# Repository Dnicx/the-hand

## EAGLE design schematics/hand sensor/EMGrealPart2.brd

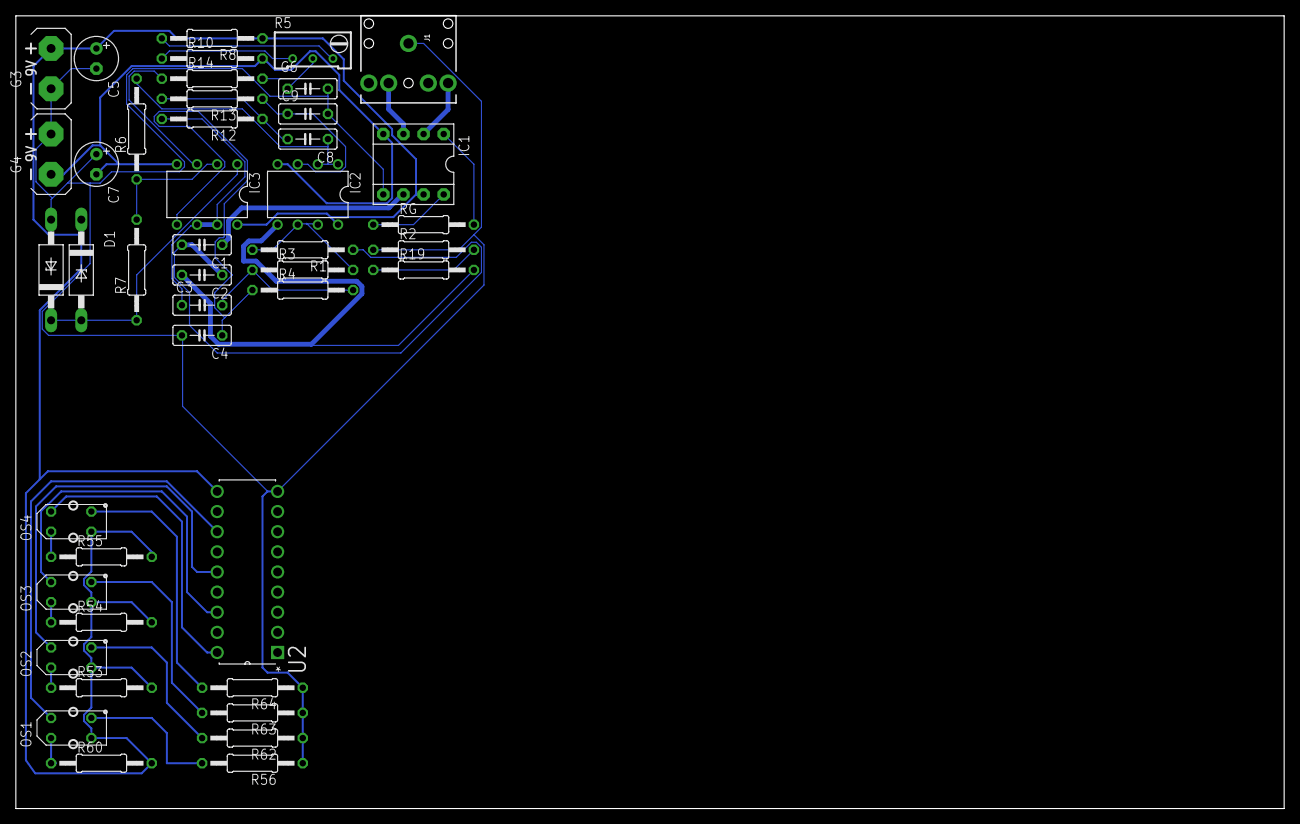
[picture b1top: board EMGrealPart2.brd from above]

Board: 2 copper layers, 160.0 x 100.0 mm, 44 parts (0 on the bottom side), 36 nets.

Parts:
C1, C2: 220nF; C050-025X075
C3: 33nF; C050-025X075
C4: 22nF; C050-025X075
C5, C7: 100u; E2,5-6
C6, C9: 10nF; C050-025X075
C8: 100nF; C050-025X075
D1, D2: F126Z12
G3, G4: DC 9V AC 0; AB9V
IC1: INA118P; DIL08
IC2, IC3: OP275P; DIL08
J1: AUDIO_JACK_3.5MM_PTH; AUDIO-JACK
OS1, OS2, OS3, OS4: TCRT5000
R1: 51K; 0207/12
R2, R19, R56, R62, R63, R64: 51k; 0207/12
R3: 6.8k; 0207/12
R4, R13: 20k; 0207/12
R5: RTRIM64W
R6, R14: 1K; 0207/12
R7: 100K; 0207/12
R8, R10: 10k; 0207/12
R12: 5.1k; 0207/12
R53, R54, R55, R60: 150; 0207/12
RG: 1K; 0207/12
U2: ULN2803AN; DIP254P762X393-18

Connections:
0: C4.2, C5.-, C6.2, C7.+, C9.2, D2.A, G3.-, G4.+, IC1.5, J1.SLEEVE, R2.1, R56.1, R62.1, R63.1, R64.1, U2.9
+9V: C5.+, D1.C, G3.+, IC1.7, IC2.8, IC3.8, OS1.C, OS2.C, OS3.C, OS4.C, R8.1, R53.2, R54.2, R55.2, R60.2, U2.10
-9V: C7.-, G4.-, IC1.4, IC2.4, IC3.4, R10.2
unnamed: IC1.1, RG.2
unnamed: IC1.8, RG.1
unnamed: IC1.2, J1.RING
unnamed: C8.2, R12.1, R13.2
unnamed: C1.2, C2.1, R1.1
unnamed: C1.1, IC1.6
unnamed: C2.2, IC2.5, R19.2
unnamed: IC2.6, IC2.7, R1.2, R3.2
unnamed: C3.2, R3.1, R4.2
unnamed: C4.1, IC3.5, R4.1
unnamed: C3.1, IC3.6, IC3.7, R12.2
unnamed: D1.A, D2.C, IC3.1, R7.1
unnamed: C9.1, IC2.3, R13.1
unnamed: R5.1, R10.1
unnamed: C6.1, R5.2, R14.2
unnamed: IC3.2, R6.1, R7.2
unnamed: R2.2, R19.1
unnamed: C8.1, IC2.1, IC2.2, R6.2
unnamed: R5.3, R8.2
unnamed: OS4.K, U2.18
unnamed: OS3.K, U2.16
unnamed: OS2.K, U2.14
unnamed: OS1.K, U2.12
unnamed: IC3.3, R14.1
unnamed: IC1.3, J1.TSH
unnamed: OS1.E, R56.2
unnamed: OS2.E, R62.2
unnamed: OS3.E, R63.2
unnamed: OS4.E, R64.2
unnamed: OS4.A, R55.1
unnamed: OS3.A, R54.1
unnamed: OS2.A, R53.1
unnamed: OS1.A, R60.1

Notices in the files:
parts and their libraries:
SparkFun-Connectors: Licensing: Creative Commons ShareAlike 4.0 International - https://creativecommons.org/licenses/by-sa/4.0
